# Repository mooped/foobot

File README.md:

# foobot
Robot table football using cheap 433mhz radio modules and classic Nintendo and Sega controllers

[Foobot blog article](http://www.moop.org.uk/index.php/2015/03/15/foobot/)

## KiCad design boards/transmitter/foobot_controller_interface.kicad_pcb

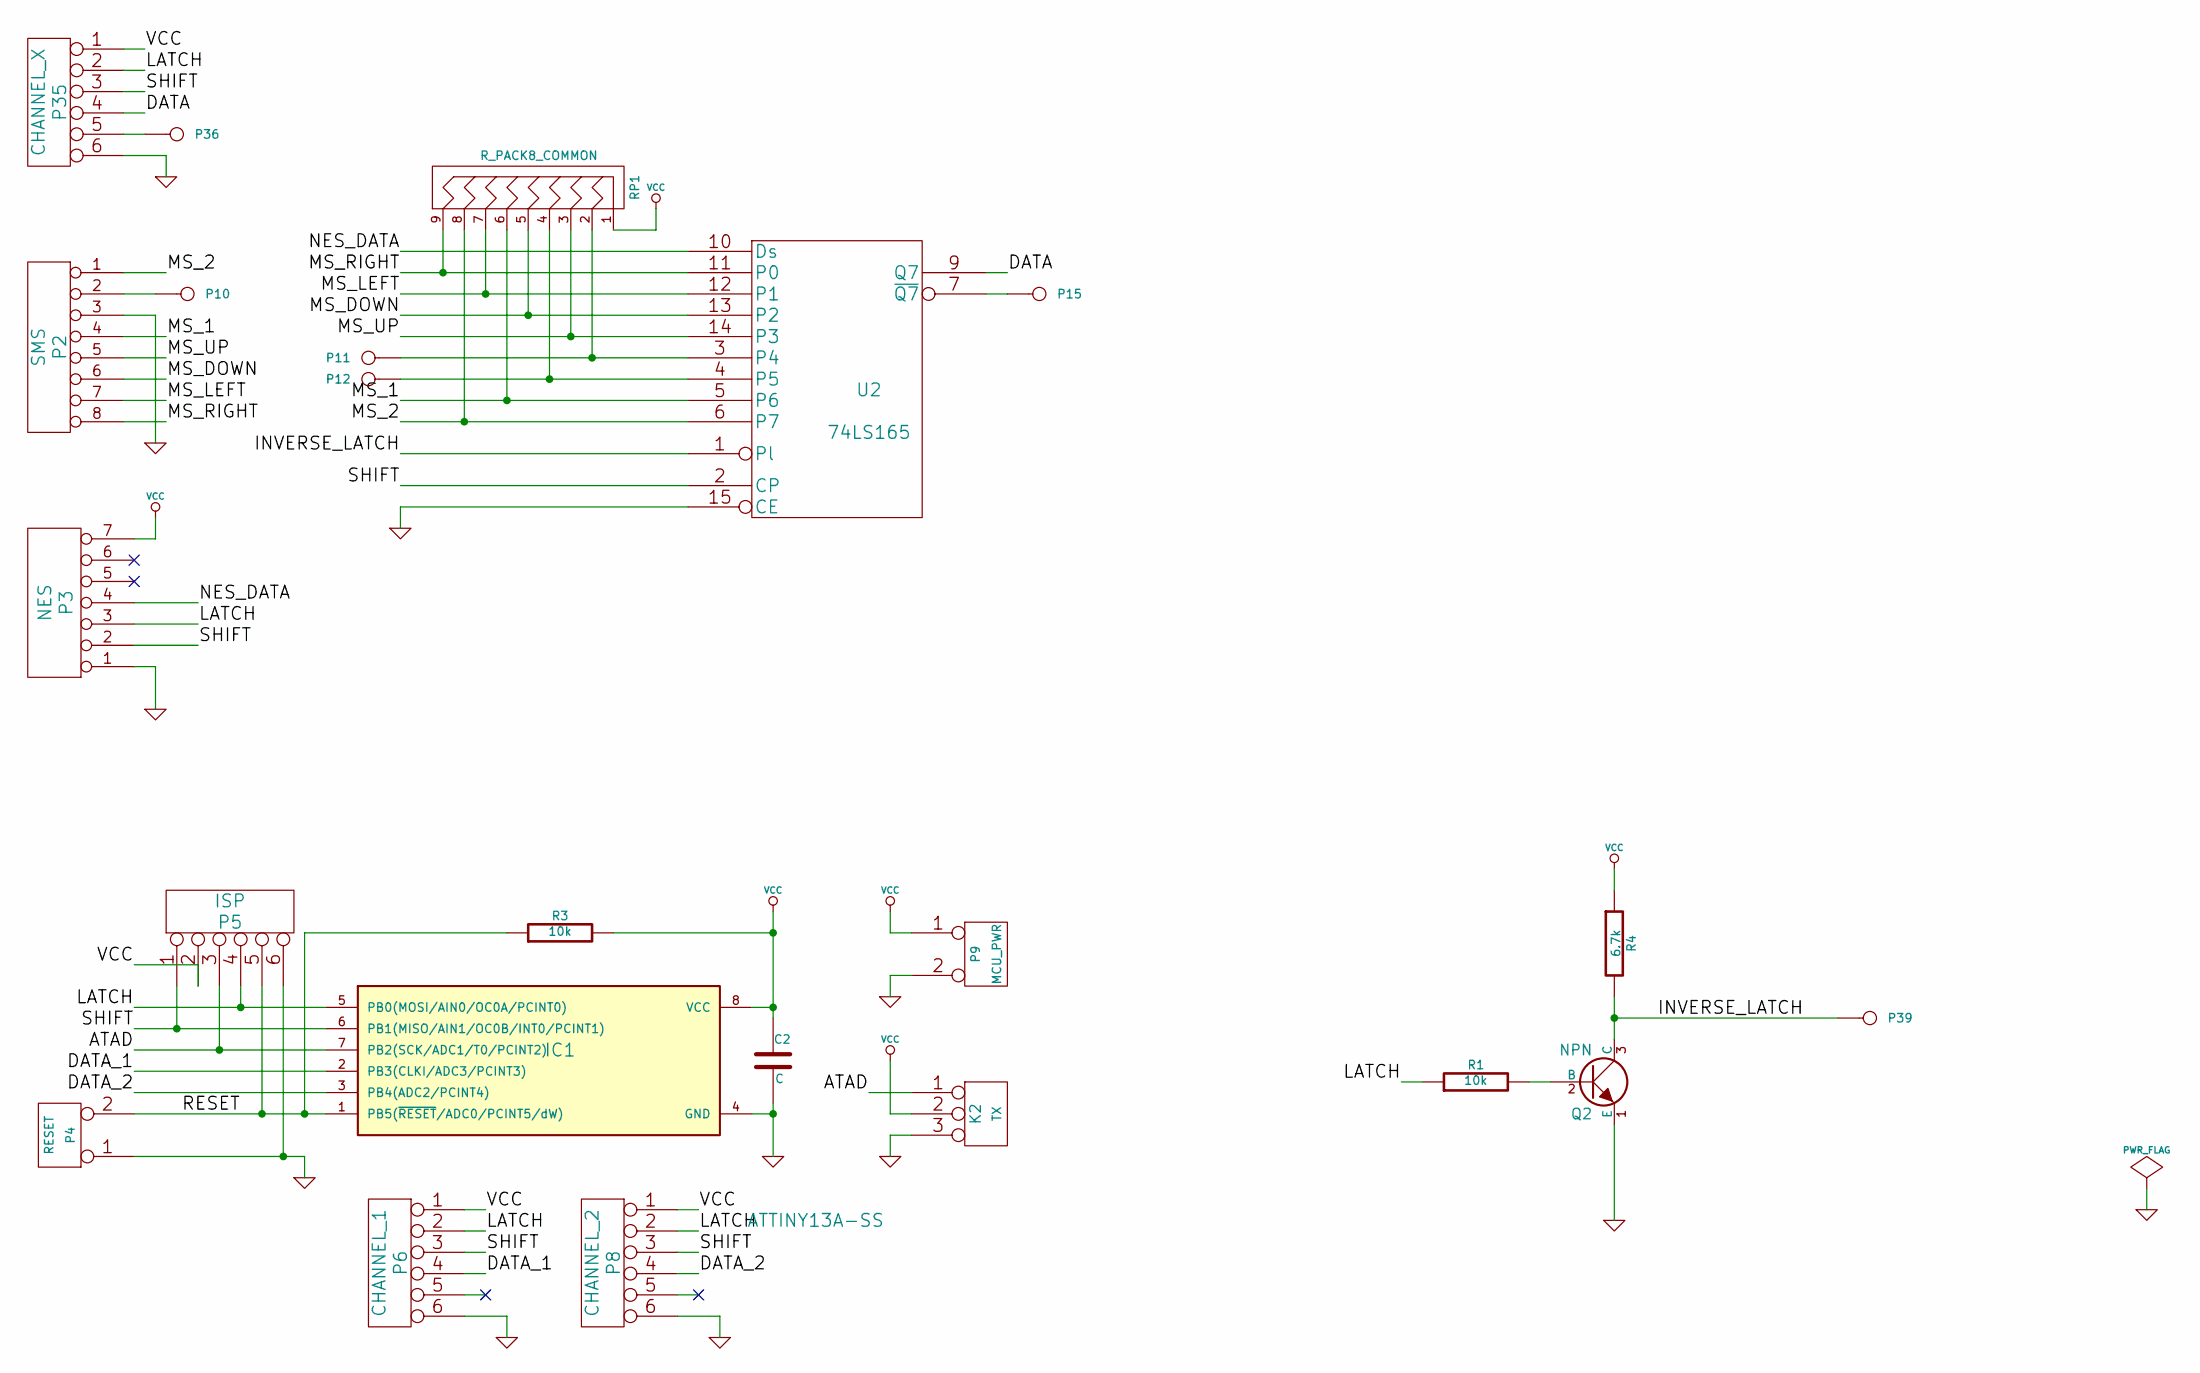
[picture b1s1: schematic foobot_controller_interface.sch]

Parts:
C2: C
IC1: ATTINY13A-SS; SO8
K2: TX
P2: SMS
P3: NES
P4: RESET
P5: ISP
P6: CHANNEL_1
P8: CHANNEL_2
P9: MCU_PWR
P10: AUX_IN
P11, P12: AUX
P15: ¬Q7
P35: CHANNEL_X
P36: CONN_1
P39: ¬LATCH
Q2: NPN
R1, R3: 10k
R4: 6.7k
RP1: R_PACK8_COMMON
U2: 74LS165

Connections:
/ATAD: IC1.7 (PB2(SCK/ADC1/T0/PCINT2)), K2.1, P5.3
/DATA: P35.4, U2.9 (Q7)
/DATA_1: IC1.2 (PB3(CLKI/ADC3/PCINT3)), P6.4
/DATA_2: IC1.3 (PB4(ADC2/PCINT4)), P8.4
/INVERSE_LATCH: P39.1, Q2.3 (C), R4.2, U2.1 (Pl)
/LATCH: IC1.5 (PB0(MOSI/AIN0/OC0A/PCINT0)), P3.3, P5.4, P6.2, P8.2, P35.2, R1.1; also elsewhere on the board
/MS_1: P2.4, RP1.6, U2.5 (P6); also elsewhere on the board
/MS_2: P2.1, RP1.8, U2.6 (P7); also elsewhere on the board
/MS_DOWN: P2.6, RP1.5, U2.13 (P2); also elsewhere on the board
/MS_LEFT: P2.7, RP1.7, U2.12 (P1); also elsewhere on the board
/MS_RIGHT: P2.8, RP1.9 (R8), U2.11 (P0); also elsewhere on the board
/MS_UP: P2.5, RP1.3, U2.14 (P3); also elsewhere on the board
/NES_DATA: P3.4, U2.10 (Ds); also elsewhere on the board
/RESET: IC1.1 (PB5(~RESET~/ADC0/PCINT5/dW)), P4.2 (PM), P5.5, R3.1
/SHIFT: IC1.6 (PB1(MISO/AIN1/OC0B/INT0/PCINT1)), P3.2, P5.1, P6.3, P8.3, P35.3, U2.2 (CP); also elsewhere on the board
GND: C2.2, IC1.4 (GND), K2.3, P2.3, P3.1, P4.1, P5.6, P6.6, P8.6, P9.2 (PM), P35.6, Q2.1 (E), U2.8 (GND), U2.15 (CE); also elsewhere on the board
unnamed: P35.5, P36.1
unnamed: Q2.2 (B), R1.2
unnamed: P15.1, U2.7 (~Q7)
unnamed 19: P2.2, P10.1; also elsewhere on the board
unnamed: P11.1, RP1.2, U2.3 (P4)
unnamed: P12.1, RP1.4, U2.4 (P5)
VCC: C2.1, IC1.8 (VCC), K2.2 (PM), P3.7, P5.2, P6.1, P8.1, P9.1, P35.1, R3.2, R4.1, RP1.1, U2.16 (VCC); also elsewhere on the board

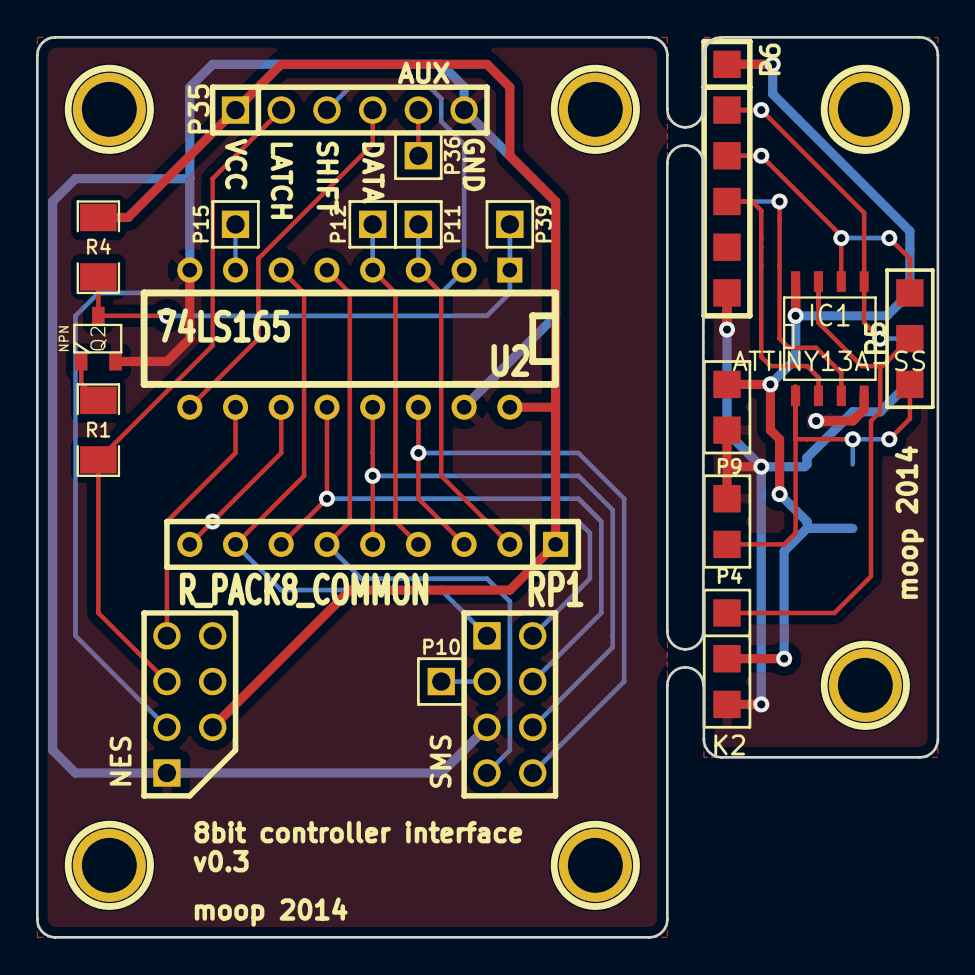
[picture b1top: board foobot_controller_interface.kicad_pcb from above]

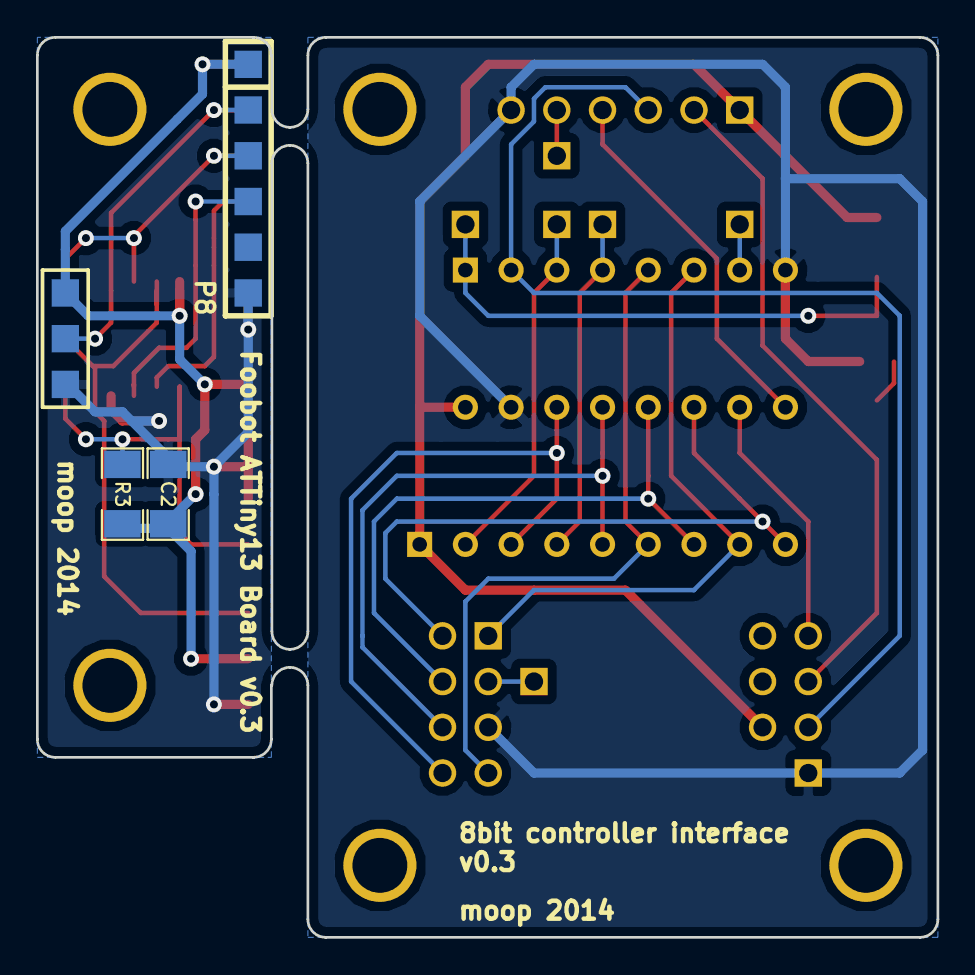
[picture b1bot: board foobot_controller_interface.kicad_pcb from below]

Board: 2 copper layers, 50.0 x 50.0 mm, 23 parts (3 on the bottom side), 23 nets.

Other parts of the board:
NES: NES; D-CANNON_COMPACT
SMS: SMS; pin_array_2x4

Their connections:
/LATCH: NES.3; also elsewhere on the board
/MS_1: SMS.4; also elsewhere on the board
/MS_2: SMS.1; also elsewhere on the board
/MS_DOWN: SMS.6; also elsewhere on the board
/MS_LEFT: SMS.7; also elsewhere on the board
/MS_RIGHT: SMS.8; also elsewhere on the board
/MS_UP: SMS.5; also elsewhere on the board
/NES_DATA: NES.4; also elsewhere on the board
/SHIFT: NES.2; also elsewhere on the board
GND: NES.1, SMS.3; also elsewhere on the board
unnamed 19: SMS.2; also elsewhere on the board
VCC: NES.7; also elsewhere on the board

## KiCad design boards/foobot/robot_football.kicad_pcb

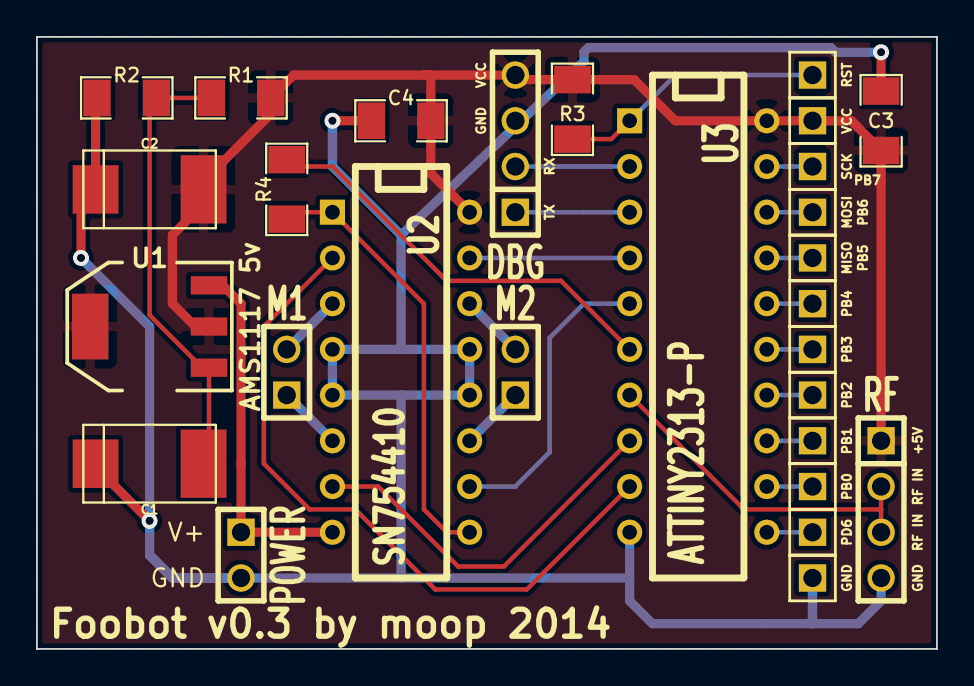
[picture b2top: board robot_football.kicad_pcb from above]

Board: 2 copper layers, 50.0 x 34.0 mm, 28 parts (0 on the bottom side), 27 nets.

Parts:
C1: 10u; c_tant_D
C2: 22u; c_tant_D
C3, C4: C; SM1206
DBG: DEBUG; SIL-4
M1: MOTOR_1; SIL-2
M2: MOTOR_2; SIL-2
P4: PB0; PIN_ARRAY_1
P5: PB1; PIN_ARRAY_1
P6: PB2; PIN_ARRAY_1
P7: PB3; PIN_ARRAY_1
P8: PB4; PIN_ARRAY_1
P10: PD6; PIN_ARRAY_1
P13: MISO; PIN_ARRAY_1
P14: SCK; PIN_ARRAY_1
P15: RST; PIN_ARRAY_1
P16: VCC; PIN_ARRAY_1
P17: MOSI; PIN_ARRAY_1
P18: GND; PIN_ARRAY_1
POWER: BATT; SIL-2
R1, R2: R; SM1206
R3, R4: 10k; SM1206
RF: RF_MOD; SIL-4
U1: AMS1117 5v; SOT223
U2: SN754410; DIP-16__300
U3: ATTINY2313-P; DIP-20__300

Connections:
+5V: C2.2, C3.1, C4.1, DBG.4, P16.1, R1.2, R3.1, RF.1, U1.2, U1.4, U2.16, U3.20
+8V: POWER.1, U1.3, U2.8
/M1_A: U2.2, U3.9
/M1_B: U2.7, U3.8
/M2_A: U2.15, U3.4
/M2_B: U2.10, U3.5
/MISO: P13.1, U3.18
/MOSI: P17.1, U3.17
/PWM: R4.1, U3.6
/RF_IN: RF.2, RF.3, U3.7
/RST: P15.1, R3.2, U3.1
/RX: DBG.2, U3.2
/SCK: P14.1, U3.19
/TX: DBG.1, U3.3
GND: C1.1, C2.1, C3.2, C4.2, DBG.3, P18.1, POWER.2, R2.1, RF.4, U2.4, U2.5, U2.12, U2.13, U3.10
unnamed: P8.1, U3.16
unnamed: P10.1, U3.11
unnamed: P4.1, U3.12
unnamed: P5.1, U3.13
unnamed: P6.1, U3.14
unnamed: P7.1, U3.15
unnamed: R4.2, U2.1, U2.9
unnamed: C1.2, R1.1, R2.2, U1.1
unnamed: M1.2, U2.3
unnamed: M2.2, U2.14
unnamed: M2.1, U2.11
unnamed: M1.1, U2.6

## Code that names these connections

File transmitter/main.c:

#include <util/delay.h>
#include <avr/interrupt.h>
#include <avr/io.h>
#include <avr/wdt.h>

#define NULL ((void*)0)

#define LATCH_PIN   PB0
#define SHIFT_PIN   PB1
#define D0_PIN      PB3
#define D1_PIN      PB4

#define ATAD_PIN    PB2

#define DDR_LATCH   DDB0
#define DDR_SHIFT   DDB1
#define DDR_D0      DDB3
#define DDR_D1      DDB4

#define DDR_ATAD    DDB2

void SetupHardware(void)
{
  wdt_disable();

  // Configure port B direction and pull ups
  DDRB |= (1<<DDR_LATCH)|(1<<DDR_SHIFT)|(1<<DDR_ATAD);
  PORTB |= (1<<D0_PIN)|(1<<D1_PIN);

  // Timer 0 setup
  TCCR0A = (1<<WGM01);                          // Clear on Compare Match (CTC) mode
  TCCR0B = (1<<CS02)|(0<<CS01)|(0<<CS00);       // CLK/256 prescaler setting
  OCR0A = 7;                                   // Compare match register - time in increments of 1/16khz
  TIMSK0 = (0<<OCIE0B)|(1<<OCIE0A)|(0<<TOIE0);  // Interrupt on OCR0A match

  // Disable pin change interrupts
  GIMSK &= ~((1<<INT0)|(1<<PCIE));

  // Enable interrupts
  sei();
}

typedef enum
{
  eTS_IDLE = 0,
  eTS_WARMUP_ZEROES,
  eTS_WARMUP_ONES,
  eTS_MESSAGE,
  eTS_TRAILER,
} ETransmissionState;

void radio_out(uint8_t value)
{
  if (value)
  {
    PORTB |= (1<<ATAD_PIN);
  }
  else
  {
    PORTB &= ~(1<<ATAD_PIN);
  }
}

// Transmission shared state
static uint8_t      state = eTS_IDLE;
static uint8_t      transmitPhase = 0;
static uint8_t      transmitCounter = 0;

// State used by eTS_MESSAGE
static const char*  pszTransmitByte = NULL;
static uint8_t      transmitBit = 0x01;
static uint8_t      messageLength = 0;

void begin_state_warmup_zeroes(void)
{
  transmitPhase = 0;
  transmitCounter = 14;
  state = eTS_WARMUP_ZEROES;
}

void begin_state_warmup_ones(void)
{
  transmitPhase = 0;
  transmitCounter = 4;
  state = eTS_WARMUP_ONES;
}

void begin_state_message(void)
{
  transmitPhase = 0;
  transmitCounter = messageLength;
  state = eTS_MESSAGE;
}

void begin_state_trailer(uint8_t value)
{
  transmitCounter = 4;
  transmitPhase = value ? 1 : 0;
  state = eTS_TRAILER;
}

void begin_transmission(const char* pszMessage, uint8_t length)
{
  // Cancel any existing trannsmission
  state = eTS_IDLE;

  // Initialise the message
  pszTransmitByte = pszMessage;
  messageLength = length;
 
  // Begin sending the message next timer interrupt
  begin_state_warmup_zeroes();
}

ISR(TIM0_COMPA_vect, ISR_BLOCK)
{
  switch (state)
  {
    case eTS_IDLE:
    {
      radio_out(0);
    } break;
    case eTS_WARMUP_ZEROES:
    {
      radio_out(!transmitPhase);
      if (transmitPhase == 1)
      {
        transmitPhase = 0;
        if (--transmitCounter == 0)
        {
          begin_state_warmup_ones();
        }
      }
      else
      {
        transmitPhase = 1;
      }
    } break;
    case eTS_WARMUP_ONES:
    {
      radio_out(transmitPhase);
      if (transmitPhase == 1)
      {
        transmitPhase = 0;
        if (--transmitCounter == 0)
        {
          begin_state_message();
        }
      }
      else
      {
        transmitPhase = 1;
      }
    } break;
    case eTS_MESSAGE:
    {
      const uint8_t out = ((*pszTransmitByte) & transmitBit) ? transmitPhase : !transmitPhase;
      radio_out(out);
      if (transmitPhase == 1)
      {
        if (transmitBit == (1<<7))
        {
          ++pszTransmitByte;
          transmitBit = 0x01;
          if (--transmitCounter == 0)
          {
            begin_state_trailer(!out);
          }
        }
        else
        {
          transmitBit = transmitBit <<  1;
        }
        transmitPhase = 0;
      }
      else
      {
        transmitPhase = 1;
      }
    } break;
    case eTS_TRAILER:
    {
      radio_out(transmitPhase);
      if (--transmitCounter == 0)
      {
        state = eTS_IDLE;
      }
    } break;
    default:
    {
      radio_out(0);
      state = eTS_IDLE;
    } break;
  }
  return;
}

static char joypadTransmitBuffer[4] = {0};

uint16_t wheel = 0;

uint8_t inputs[2][2] = {
  {0, 0},
  {0, 0},
};

// Map robots to a controller channel, index and callsign
typedef struct
{
  uint8_t   channel;
  uint8_t   index;
  char      callsign;
} SRobotMap;

#define NUM_ROBOTS 4
static const SRobotMap robot_map[NUM_ROBOTS] = {
  { 0, 0, '1' },
  { 0, 1, 'a' },
  { 1, 0, '2' },
  { 1, 1, 'b' },
};

uint8_t current_robot = 0;

int main(void)
{
  SetupHardware();

  for (;;)
  {
    // If idle, process controller inputs and transmit appropriate messages
    if (state == eTS_IDLE)
    {
      // Serially read from 4 controllers (2 chains of 2 controllers)
      {
        PORTB |= (1<<LATCH_PIN);  // Enable the latch line
        _delay_us(12);
        PORTB &= ~(1<<LATCH_PIN);
        _delay_us(6);
  
        // Loop on controller index
        for (int controller_index = 0; controller_index < 2; ++controller_index)
        {
          inputs[0][controller_index] = 0;
          inputs[1][controller_index] = 0;

          // Read 8 bits from each line (read first, then send the next clock)
          for (int i = 0; i < 8; ++i)
          {
            inputs[0][controller_index] <<= 1;
            inputs[1][controller_index] <<= 1;
            inputs[0][controller_index] |= !(PINB & (1<<D0_PIN));
            inputs[1][controller_index] |= !(PINB & (1<<D1_PIN));

            PORTB |= (1<<SHIFT_PIN);
            _delay_us(6);
            PORTB &= ~(1<<SHIFT_PIN);
            _delay_us(6);
          }
        }

        // Transmit controller data for the current robot
        const SRobotMap* pRobot = &robot_map[current_robot];
        const uint8_t padstate = inputs[pRobot->channel][pRobot->index];
        
        joypadTransmitBuffer[0] = pRobot->callsign;
        joypadTransmitBuffer[1] = (padstate & 0x3f) | ((padstate >> 2) & 0x30); // Avoid using upper bits
        joypadTransmitBuffer[2] = ~(joypadTransmitBuffer[1]);
        joypadTransmitBuffer[3] = '\r';
        begin_transmission(joypadTransmitBuffer, 3);

        if (++current_robot >= NUM_ROBOTS)
        {
          current_robot = 0;
        }
      }
    }
    else
    {
      PORTB &= ~(1<<SHIFT_PIN);
    }
  }
}

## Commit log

2014-10-26 Initial commit - generate a pulse via a Minimus.
2014-10-29 Initial setup with timed interrupt on input signal change and debug output on Port A.
2014-10-29 Seemingly correctly connect the letter 'z' in a transmission.
2014-10-30 Correct recovery of manchester coded message. Each recieved byte is echoed through the UART.
2014-10-30 Refactor to call a handler function for each byte.
2014-10-30 Add a handler for the start of the message.
2014-10-30 Accept motor control commands in format <robot id><q|a|z|e|d|c><!>
2014-12-09 Expect a byte of raw controller input, with a the inverse of the input as a checksum.
2015-01-07 Fix left and right.
2015-01-11 Add partially working transmitter code for ATTiny13. Reorganise directory structure.
2015-01-15 Add .gitignore.
2015-01-15 Typo fix in comment.
2015-01-18 Tweak timings for succesful transmission.
2015-01-25 Fix turning left/right while moving. Use PWM to make the speed of the robot manageable while turning/spinning.
2015-01-25 Soften the controls further.
2015-03-15 Initial implementation of over the air EEPROM settings update.
2015-03-15 Import current revision of the boards.
2015-03-15 Add MIT license
2015-03-15 Add CAD files for the robots and the controller.
2015-03-15 Add some much needed brackets to the PWM macros.
2015-03-15 Add blog article to the readme.
2015-03-16 Tweak initial PWM settings for less aggressive handling.
2015-03-20 Fix microcontroller location in foobot_controller_interface.sch Plot schematics for the circuits.
2018-11-10 Initial commit - reading data from the FooBot controller interface/transmitter is working.
2018-11-10 Station code transmitting but crashing
2018-11-11 Pre-tearing everything apart.
2018-11-11 Simplify by sending all bot commands in a single packet, since we are broadcasting anyway.
2018-11-11 Working but slow communication from station to bots.
2018-11-11 Spin the motors forward for half a second on boot.
2018-11-12 Implement SPI controller input.
2018-11-12 Implement per bot config to account for reversed motors.
2018-11-12 Fix SPI timing. Setup robot configs for their motor orientations. Fix control decoding.
2018-11-15 Flash LED on boot.
2018-11-15 Read battery voltage on boot.
2018-11-17 CAD for v2
2022-05-30 New copy of the codebase using the new ESP IDF and starting with a WebSocket for comms.
2022-05-31 Add hacky support for static files (with xxd -i for now). Add virtualjoystick.js for onscreen joystick.
2022-05-31 Add a limit to the joystick.
2022-05-31 JSON websocket payload. Working (non-PWM) motor control.
2022-06-01 Test passcode scheme.
2022-06-07 Serve web content from a SPIFFS partition.
